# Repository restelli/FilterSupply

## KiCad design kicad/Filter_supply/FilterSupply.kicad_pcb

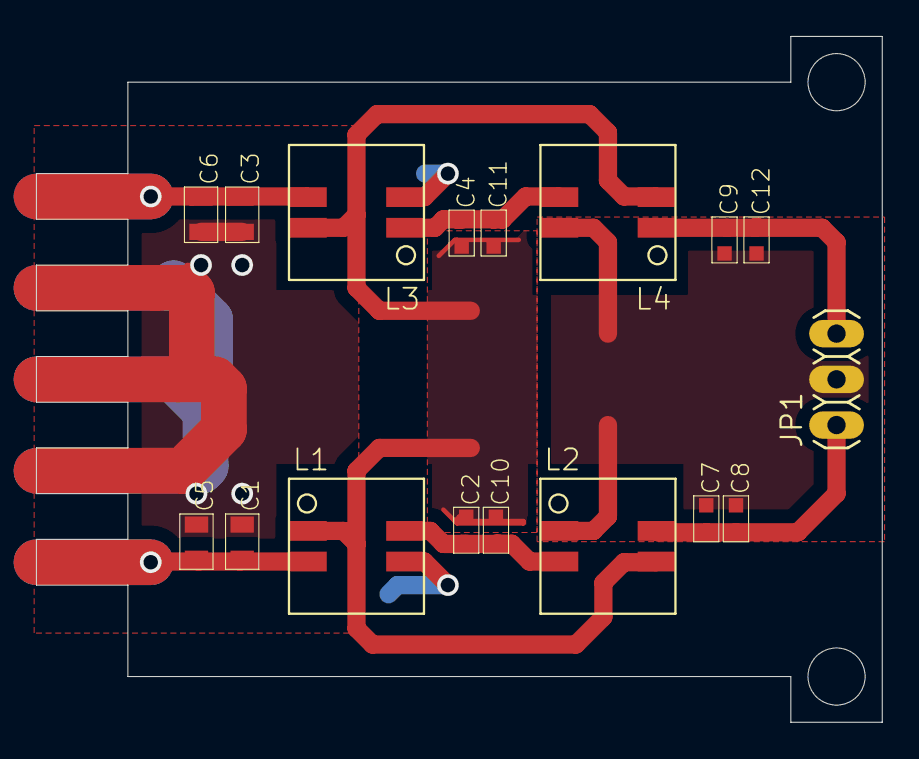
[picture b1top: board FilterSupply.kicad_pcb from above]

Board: 2 copper layers, 47.0 x 38.1 mm, 19 parts (0 on the bottom side), 9 nets.

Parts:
@HOLE0, @HOLE1: (no value)
C1, C3, C5, C6: C_MLCC_0805
C2, C4, C7, C8, C9, C10, C11, C12: C_MLCC_0603
JP1: 1X03
L1, L2, L3, L4: MSD7342

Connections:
+15V: C1.P$2, C5.P$2, L1.2
-15V: C3.P$1, C6.P$1, L3.3
COM1: C1.P$1, C3.P$2, C5.P$1, C6.P$2, L1.3, L3.2
GND: C7.P$1, C8.P$1, C9.P$2, C12.P$2, JP1.2, L2.1, L4.4
unnamed: C2.P$2, C10.P$2, L1.4, L2.2
unnamed: C2.P$1, C4.P$2, C10.P$1, C11.P$2, L1.1, L2.3, L3.4, L4.2
unnamed: C4.P$1, C11.P$1, L3.1, L4.3
V+: C7.P$2, C8.P$2, JP1.1, L2.4
V-: C9.P$1, C12.P$1, JP1.3, L4.1

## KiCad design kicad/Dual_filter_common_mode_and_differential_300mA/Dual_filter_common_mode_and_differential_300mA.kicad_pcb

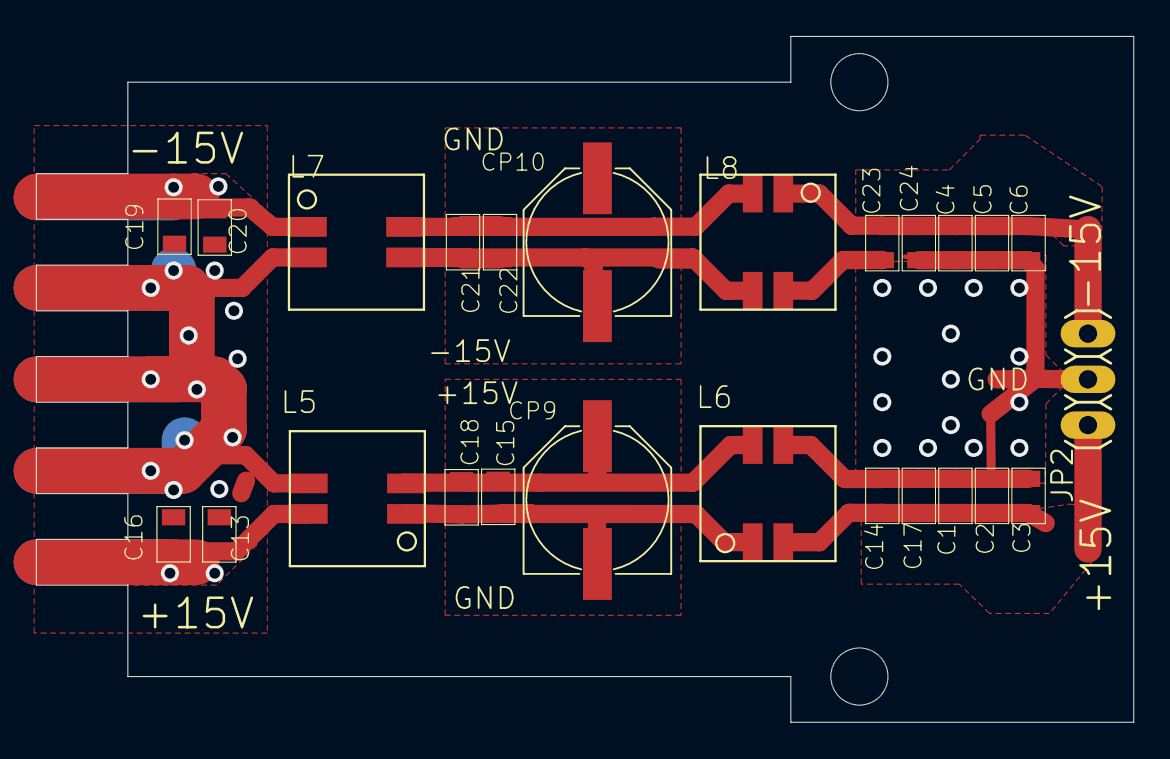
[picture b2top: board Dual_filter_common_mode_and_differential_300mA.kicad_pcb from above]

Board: 2 copper layers, 61.0 x 38.1 mm, 27 parts (0 on the bottom side), 10 nets.

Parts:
@HOLE0, @HOLE1: (no value)
C1, C2, C3, C4, C5, C6, C16, C17, C19, C24: 22uF; C_MLCC_0805
C13, C14, C15, C20, C22, C23: 1uF; C_MLCC_0805
C18, C21: DNP; C_MLCC_0805
CP9, CP10: PANASONIC_F
JP2: 1X03
L5, L6, L7, L8: MSD7342

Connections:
+15V2: C13.P$2, C16.P$2, L5.4
-15V2: C21.P$2, C22.P$2, CP10.+, L7.4, L8.2
COM2: C13.P$1, C16.P$1, C19.P$2, C20.P$2, L5.3, L7.2
GND2: C1.P$1, C2.P$1, C3.P$1, C4.P$2, C5.P$2, C6.P$2, C14.P$1, C17.P$1, C23.P$2, C24.P$2, JP2.2, L6.3, L8.4
unnamed: C15.P$2, C18.P$2, CP9.+, L5.2, L6.4
unnamed: C15.P$1, C18.P$1, CP9.-, L5.1, L6.1
unnamed: C21.P$1, C22.P$1, CP10.-, L7.3, L8.3
unnamed: C4.P$1, C5.P$1, C6.P$1, C23.P$1, C24.P$1, JP2.3, L8.1
unnamed: C19.P$1, C20.P$1, L7.1
V+2: C1.P$2, C2.P$2, C3.P$2, C14.P$2, C17.P$2, JP2.1, L6.2

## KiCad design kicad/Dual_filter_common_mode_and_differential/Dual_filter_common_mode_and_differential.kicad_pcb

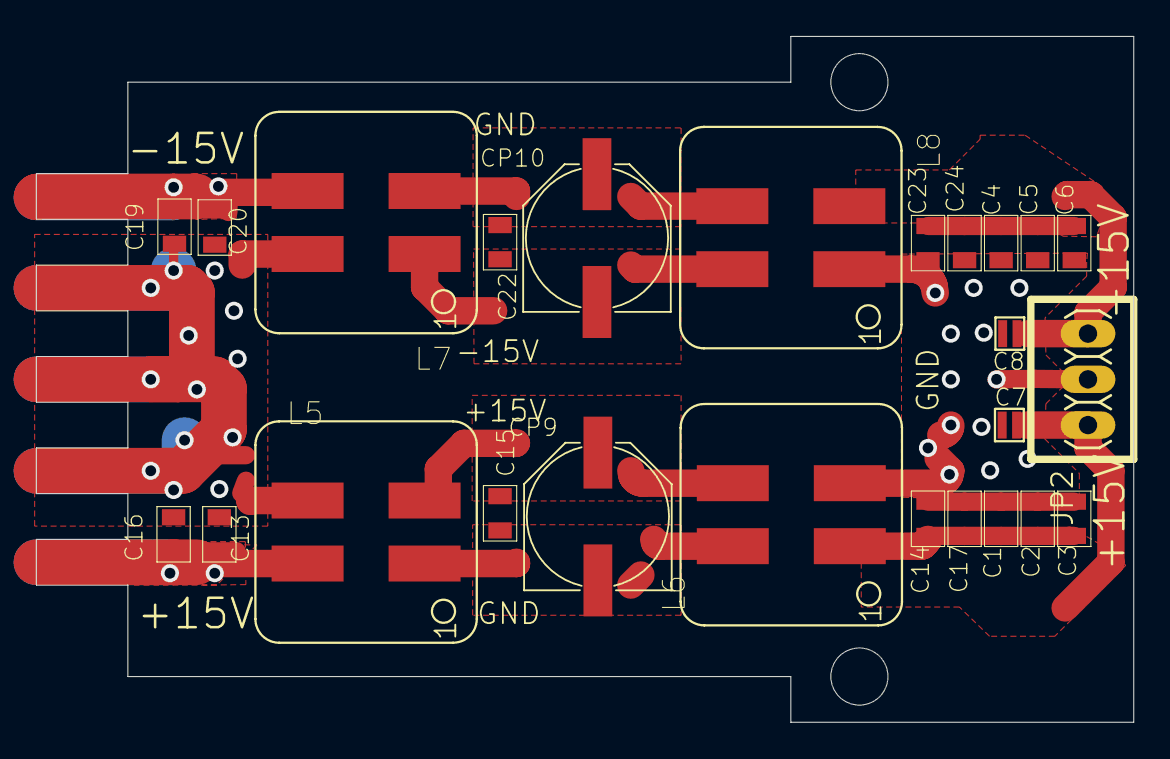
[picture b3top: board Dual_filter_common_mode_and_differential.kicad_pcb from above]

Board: 2 copper layers, 61.0 x 38.1 mm, 27 parts (0 on the bottom side), 10 nets.

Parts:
@HOLE0, @HOLE1: (no value)
C1, C2, C3, C4, C5, C6, C16, C17, C19, C24: 22uF; C_MLCC_0805
C7, C8: 22nF; C_MLCC_0306
C13, C14, C15, C20, C22, C23: 1uF; C_MLCC_0805
CP9, CP10: PANASONIC_F
JP2: 1X03
L5, L6, L7, L8: 1mH; COILCRAFT_TRANSFORMER_MSD1260

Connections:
+15V2: C13.P$2, C16.P$2, L5.P$4
-15V2: C19.P$1, C20.P$1, L7.P$3
COM2: C13.P$1, C16.P$1, C19.P$2, C20.P$2, L5.P$3, L7.P$4
GND2: C1.P$1, C2.P$1, C3.P$1, C4.P$2, C5.P$2, C6.P$2, C7.P$1, C8.P$2, C14.P$1, C17.P$1, C23.P$2, C24.P$2, JP2.2, L6.P$2, L8.P$1
unnamed: C15.P$2, CP9.+, L5.P$2, L6.P$3
unnamed: C15.P$1, CP9.-, L5.P$1, L6.P$4
unnamed: C22.P$2, CP10.+, L7.P$2, L8.P$3
unnamed: C22.P$1, CP10.-, L7.P$1, L8.P$4
unnamed: C4.P$1, C5.P$1, C6.P$1, C8.P$1, C23.P$1, C24.P$1, JP2.3, L8.P$2
V+2: C1.P$2, C2.P$2, C3.P$2, C7.P$2, C14.P$2, C17.P$2, JP2.1, L6.P$1

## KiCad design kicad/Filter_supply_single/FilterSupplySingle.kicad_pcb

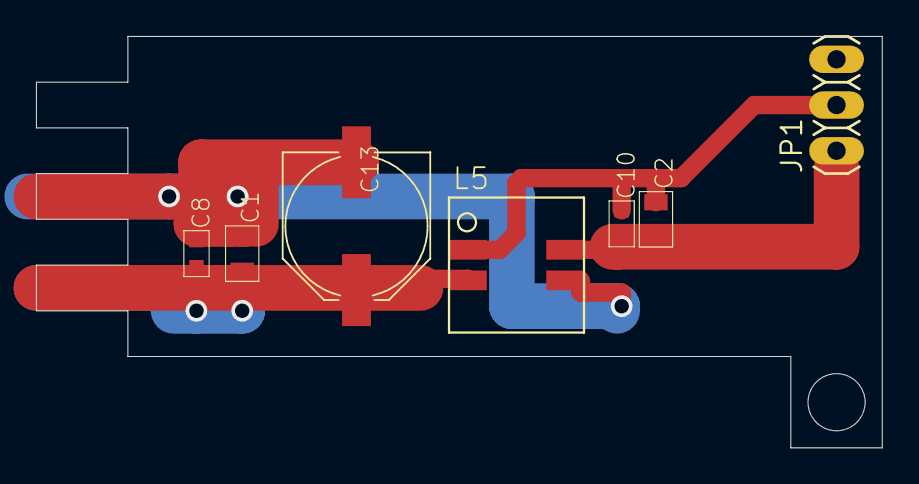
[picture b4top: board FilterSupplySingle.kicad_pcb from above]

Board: 2 copper layers, 47.0 x 22.9 mm, 8 parts (0 on the bottom side), 4 nets.

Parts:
@HOLE0: (no value)
C1, C2: C_MLCC_0805
C8, C10: C_MLCC_0603
C13: PANASONIC_F
JP1: 1X03
L5: MSD7342

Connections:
+15V: C1.P$2, C8.P$2, C13.+, L5.2
GND: C2.P$1, C10.P$1, JP1.2, L5.1
unnamed: C1.P$1, C8.P$1, C13.-, L5.3
V+: C2.P$2, C10.P$2, JP1.1, L5.4

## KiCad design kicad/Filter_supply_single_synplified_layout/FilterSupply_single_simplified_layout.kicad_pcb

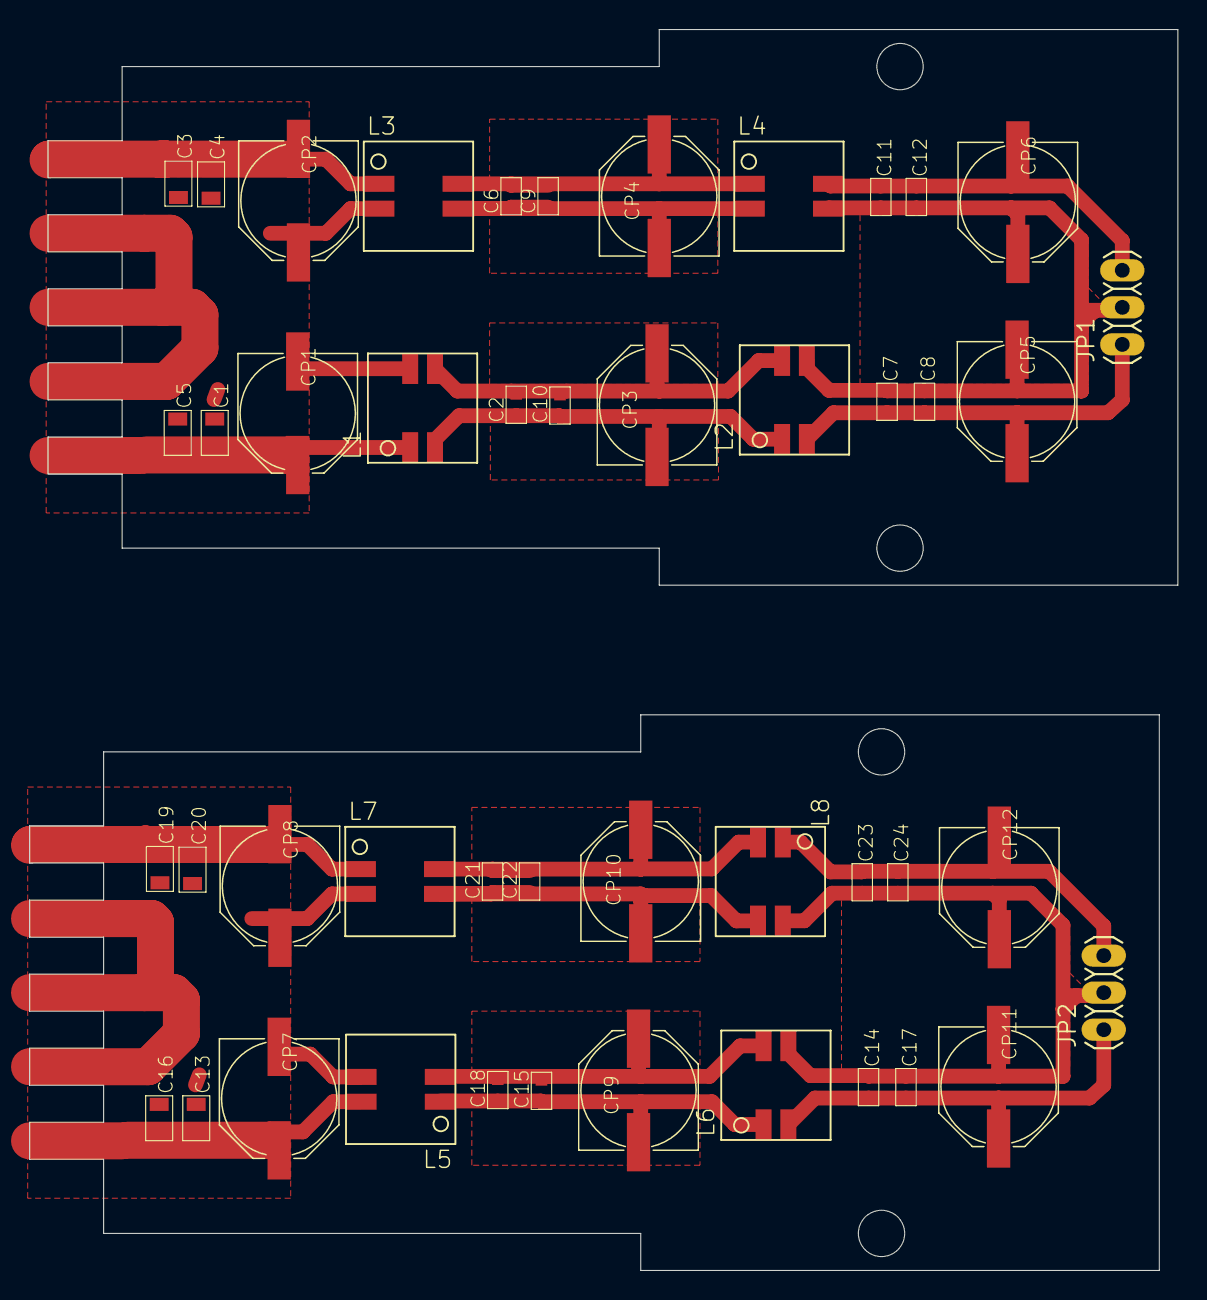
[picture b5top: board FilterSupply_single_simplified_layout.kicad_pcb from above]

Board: 2 copper layers, 78.7 x 85.1 mm, 50 parts (0 on the bottom side), 20 nets.

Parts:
@HOLE0, @HOLE1, @HOLE2, @HOLE3: (no value)
C1, C3, C4, C5, C13, C16, C19, C20: C_MLCC_0805
C2, C6, C7, C8, C9, C10, C11, C12, C14, C15, C17, C18, C21, C22, C23, C24: C_MLCC_0603
CP1, CP2, CP3, CP4, CP5, CP6, CP7, CP8, CP9, CP10, CP11, CP12: PANASONIC_F
JP1, JP2: 1X03
L1, L2, L3, L4, L5, L6, L7, L8: MSD7342

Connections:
+15V: C1.P$2, C5.P$2, CP1.+, L1.1
+15V2: C13.P$1, C16.P$1, C19.P$2, C20.P$2, CP7.-, CP8.+, L5.3, L7.2
-15V: C6.P$2, C9.P$2, CP4.+, L3.4, L4.1
-15V2: C21.P$1, C22.P$1, CP10.-, L7.3, L8.3
COM1: C1.P$1, C3.P$2, C4.P$2, C5.P$1, CP1.-, CP2.+, L1.4, L3.2
COM2: C15.P$1, C18.P$1, CP9.-, L5.1, L6.1
GND: C7.P$1, C8.P$1, C11.P$2, C12.P$2, CP5.-, CP6.+, JP1.2, L2.3, L4.3
GND2: C14.P$2, C17.P$2, CP11.+, JP2.1, L6.2
unnamed: C2.P$2, C10.P$2, CP3.+, L1.3, L2.4
unnamed: C3.P$1, C4.P$1, CP2.-, L3.1
unnamed: C2.P$1, C10.P$1, CP3.-, L1.2, L2.1
unnamed: C6.P$1, C9.P$1, CP4.-, L3.3, L4.2
unnamed: C11.P$1, C12.P$1, CP6.-, JP1.3, L4.4
unnamed: C14.P$1, C17.P$1, C23.P$2, C24.P$2, CP11.-, CP12.+, JP2.2, L6.3, L8.4
unnamed: C19.P$1, C20.P$1, CP8.-, L7.1
unnamed: C15.P$2, C18.P$2, CP9.+, L5.2, L6.4
unnamed: C23.P$1, C24.P$1, CP12.-, JP2.3, L8.1
unnamed: C21.P$2, C22.P$2, CP10.+, L7.4, L8.2
V+: C7.P$2, C8.P$2, CP5.+, JP1.1, L2.2
V+2: C13.P$2, C16.P$2, CP7.+, L5.4

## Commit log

2022-09-21 project translated to kicad and moved to kicad folder
